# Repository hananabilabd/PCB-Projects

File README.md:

# PCB-Projects
PCB Projects by me using Eagle
## ARM based micro-processor STM32F446RC breakout board 

## STM32F413CG breakout board

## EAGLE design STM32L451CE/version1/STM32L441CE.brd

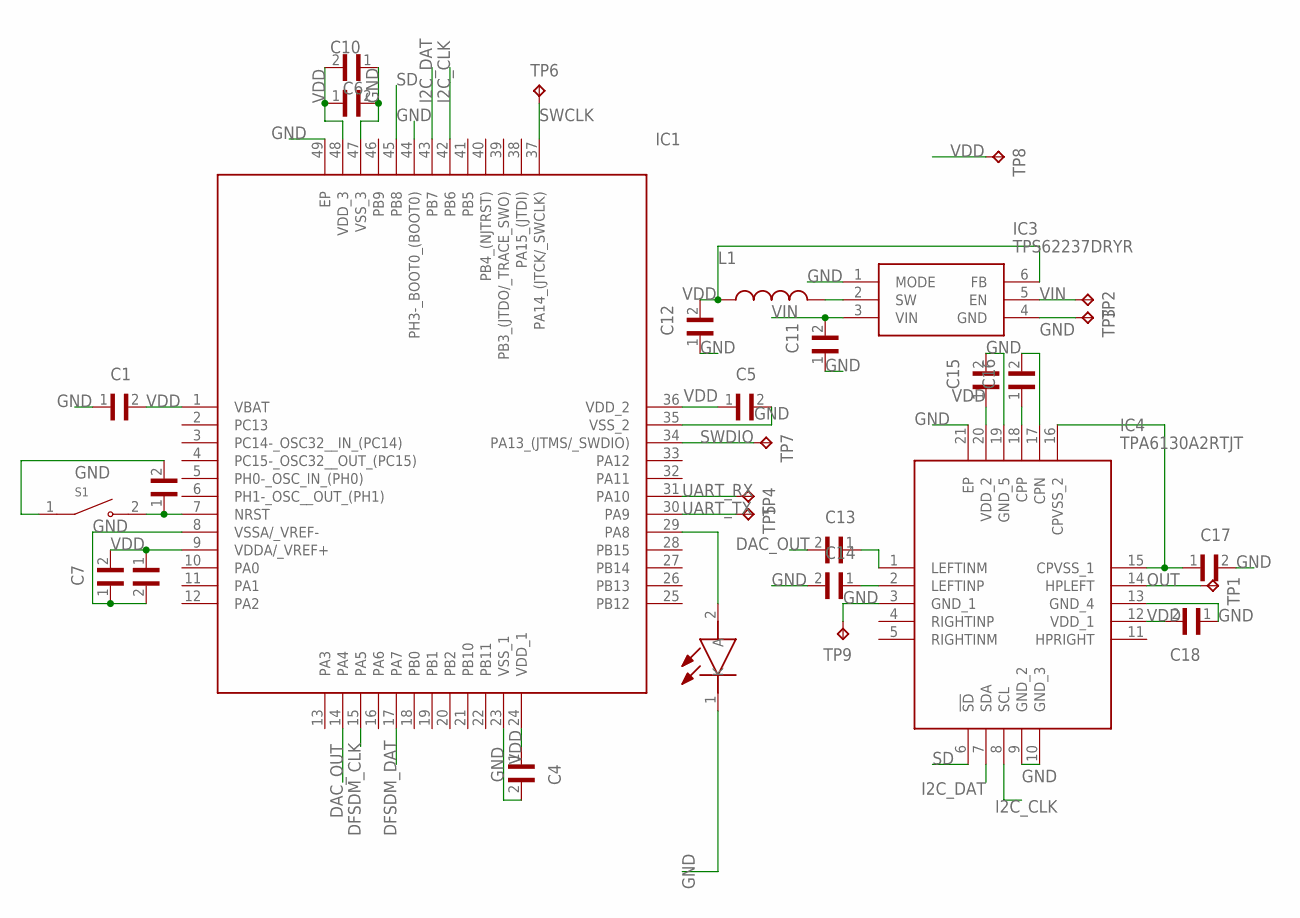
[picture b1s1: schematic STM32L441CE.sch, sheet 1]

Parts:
C1, C2, C3, C4, C5, C6: GRM033C80J104KE15D; CAPC0603X33N
C7, C15, C16, C17, C18: JMK105C6105KV-F; CAPC1005X55N
C10, C12: GRM155R60J475ME47D; CAPC1005X60N
C11: GRM155R60J225KE95D; CAPC1005X55N
C13, C14: CC0402KRX5R5BB474; CAPC1005X55N
IC1: STM32L451CEU6; QFN50P700X700X60-49N
IC3: TPS62237DRYR; SON50P100X145X60-6N
IC4: TPA6130A2RTJT; QFN50P400X400X80-21N
L1: LQM21PN2R2MC0D; INDC2012X55N
LED1: VLMS1500-GS08; VLMG1500GS08
S1: B3U-1000P; SW_B3U-1000P
TP1, TP2, TP3, TP4, TP5, TP6, TP7, TP8, TP9: TPTP11R; TP11R

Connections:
DAC_OUT: C13.2, IC1.14 (PA4)
DFSDM_CLK: IC1.15 (PA5); also elsewhere on the board
DFSDM_DAT: IC1.17 (PA7); also elsewhere on the board
GND: C1.1, C2.2, C3.2, C4.2, C5.2, C6.2, C7.1, C10.1, C11.1, C12.1, C14.2, C15.2, C17.2, C18.1, IC1.8 (VSSA/_VREF-), IC1.23 (VSS_1), IC1.35 (VSS_2), IC1.44 (PH3-_BOOT0_(BOOT0)), IC1.47 (VSS_3), IC1.49 (EP), IC3.1 (MODE), IC3.4 (GND), IC4.3 (GND_1), IC4.9 (GND_2), IC4.10 (GND_3), IC4.13 (GND_4), IC4.19 (GND_5), IC4.21 (EP), LED1.1 (K), S1.1, TP3.TP, TP9.TP; also elsewhere on the board
I2C_CLK: IC1.42 (PB6), IC4.8 (SCL)
I2C_DAT: IC1.43 (PB7), IC4.7 (SDA)
unnamed: C2.1, IC1.7 (NRST), S1.2
unnamed: IC3.2 (SW), L1.2
unnamed: C13.1, IC4.1 (LEFTINM)
unnamed: C14.1, IC4.2 (LEFTINP)
unnamed: IC1.29 (PA8), LED1.2 (A)
unnamed: C16.1, IC4.18 (CPP)
unnamed: C16.2, IC4.17 (CPN)
unnamed: C17.1, IC4.15 (CPVSS_1), IC4.16 (CPVSS_2)
OUT: IC4.14 (HPLEFT), TP1.TP
SD: IC1.45 (PB8), IC4.6 (!SD)
SWCLK: IC1.37 (PA14_(JTCK/_SWCLK)), TP6.TP
SWDIO: IC1.34 (PA13_(JTMS/_SWDIO)), TP7.TP
UART_RX: IC1.31 (PA10), TP4.TP
UART_TX: IC1.30 (PA9), TP5.TP
VDD: C1.2, C3.1, C4.1, C5.1, C6.1, C7.2, C10.2, C12.2, C15.1, C18.2, IC1.1 (VBAT), IC1.9 (VDDA/_VREF+), IC1.24 (VDD_1), IC1.36 (VDD_2), IC1.48 (VDD_3), IC3.6 (FB), IC4.12 (VDD_1), IC4.20 (VDD_2), L1.1, TP8.TP; also elsewhere on the board
VIN: C11.2, IC3.3 (VIN), IC3.5 (EN), TP2.TP

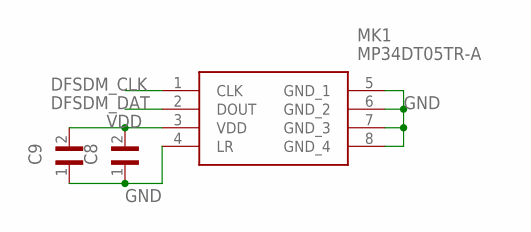
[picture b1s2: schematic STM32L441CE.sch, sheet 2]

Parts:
C8: JMK105C6105KV-F; CAPC1005X55N
C9: GRM033C80J104KE15D; CAPC0603X33N
MK1: MP34DT05TR-A; MP34DT05TRA

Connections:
DFSDM_CLK: MK1.1 (CLK); also elsewhere on the board
DFSDM_DAT: MK1.2 (DOUT); also elsewhere on the board
GND: C8.1, C9.1, MK1.4 (LR), MK1.5 (GND_1), MK1.6 (GND_2), MK1.7 (GND_3), MK1.8 (GND_4); also elsewhere on the board
VDD: C8.2, C9.2, MK1.3 (VDD); also elsewhere on the board

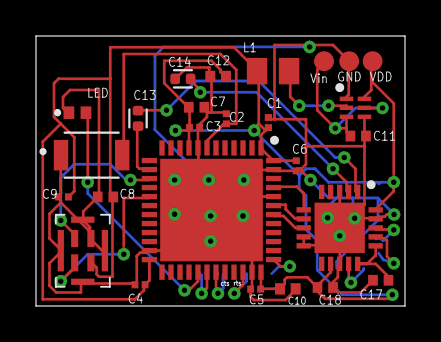
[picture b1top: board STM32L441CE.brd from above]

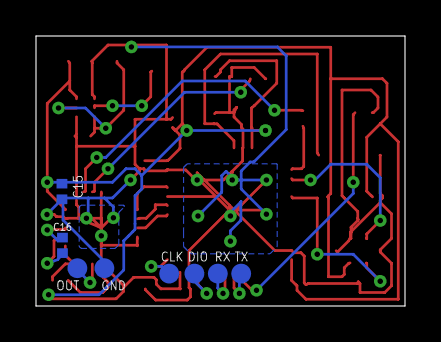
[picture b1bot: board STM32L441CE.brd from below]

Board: 2 copper layers, 20.5 x 15.0 mm, 34 parts (8 on the bottom side), 22 nets.

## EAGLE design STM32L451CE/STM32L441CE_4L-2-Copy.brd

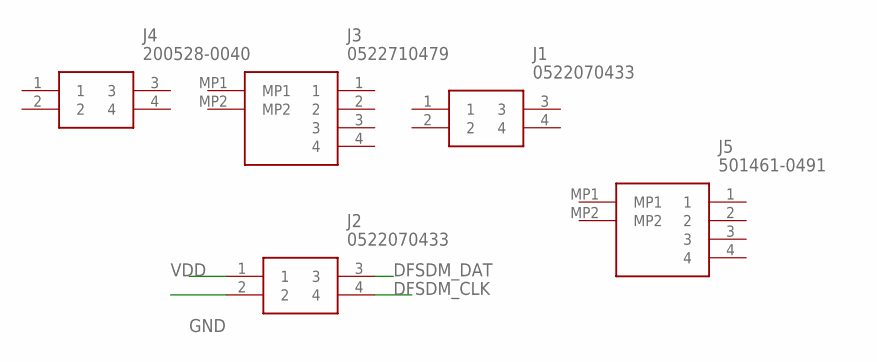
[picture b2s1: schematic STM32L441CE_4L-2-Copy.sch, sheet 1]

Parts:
J1, J2: 0522070433
J3: 0522710479
J4: 200528-0040
J5: 501461-0491; 5014610491

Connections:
DFSDM_CLK: J2.4; also elsewhere on the board
DFSDM_DAT: J2.3; also elsewhere on the board
GND: J2.2; also elsewhere on the board
VDD: J2.1; also elsewhere on the board

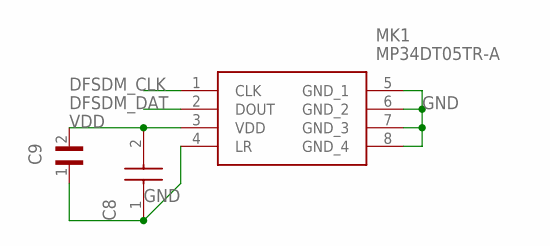
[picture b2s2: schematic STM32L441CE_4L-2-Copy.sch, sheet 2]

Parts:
C8: AMK063AC6105KP-F; CAPC0603X33N
C9: GRM033C80J104KE15D; CAPC0603X33N
MK1: MP34DT05TR-A; MP34DT05TRA

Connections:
DFSDM_CLK: MK1.1 (CLK); also elsewhere on the board
DFSDM_DAT: MK1.2 (DOUT); also elsewhere on the board
GND: C8.1, C9.1, MK1.4 (LR), MK1.5 (GND_1), MK1.6 (GND_2), MK1.7 (GND_3), MK1.8 (GND_4); also elsewhere on the board
VDD: C8.2, C9.2, MK1.3 (VDD); also elsewhere on the board

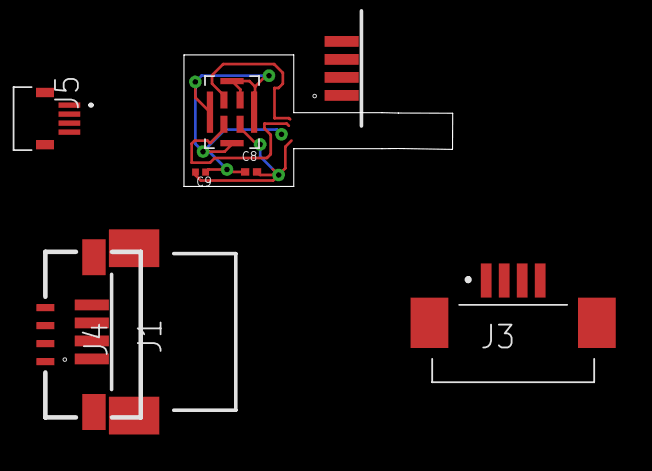
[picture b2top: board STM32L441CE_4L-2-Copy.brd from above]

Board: 4 copper layers, 14.9 x 7.3 mm, 8 parts (0 on the bottom side), 4 nets.

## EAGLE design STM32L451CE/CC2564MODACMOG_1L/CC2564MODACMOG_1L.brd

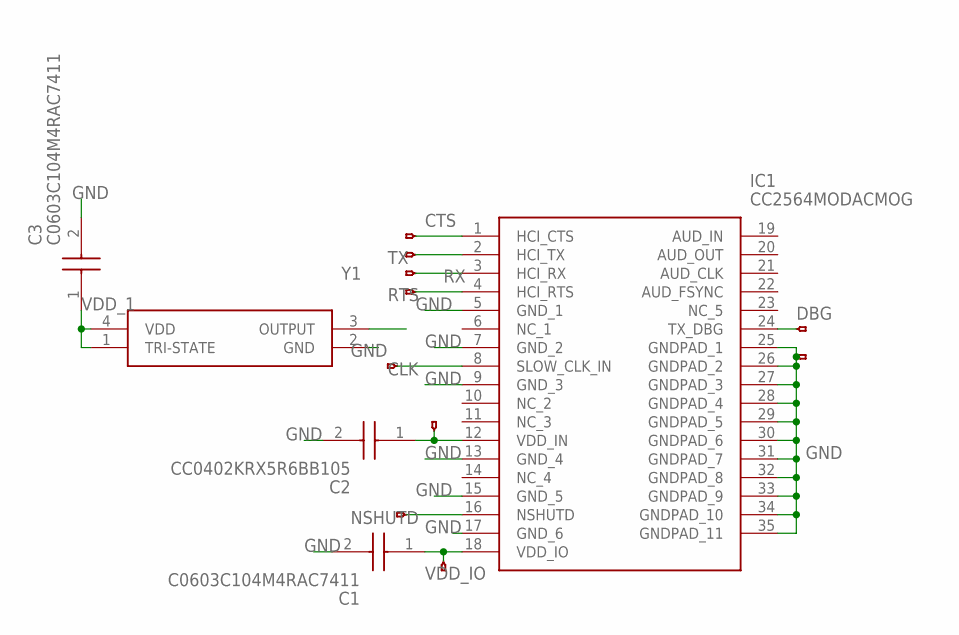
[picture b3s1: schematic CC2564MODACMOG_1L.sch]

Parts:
C1, C3: C0603C104M4RAC7411; CAPC1608X95N
C2: CC0402KRX5R6BB105; CAPC1005X55N
IC1: CC2564MODACMOG; MOG0035A
JP1, JP2, JP7, JP8, JP9, JP10, JP11, JP12, JP13, JP14: HEADERHOLE-HEADERHOLE; 1X1-HEADER-HOLE
Y1: ECS-327MVATX-1-CN-TR; ECS327MVATX1CNTR

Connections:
CLK: IC1.8 (SLOW_CLK_IN), JP11.1
CTS: IC1.1 (HCI_CTS), JP7.1
DBG: IC1.24 (TX_DBG), JP2.1
GND: C1.2, C2.2 (C2), C3.2, IC1.5 (GND_1), IC1.7 (GND_2), IC1.9 (GND_3), IC1.13 (GND_4), IC1.15 (GND_5), IC1.17 (GND_6), IC1.25 (GNDPAD_1), IC1.26 (GNDPAD_2), IC1.27 (GNDPAD_3), IC1.28 (GNDPAD_4), IC1.29 (GNDPAD_5), IC1.30 (GNDPAD_6), IC1.31 (GNDPAD_7), IC1.32 (GNDPAD_8), IC1.33 (GNDPAD_9), IC1.34 (GNDPAD_10), IC1.35 (GNDPAD_11), JP1.1, Y1.2 (GND)
NSHUTD: IC1.16 (NSHUTD), JP14.1
RTS: IC1.4 (HCI_RTS), JP10.1
RX: IC1.3 (HCI_RX), JP9.1
TX: IC1.2 (HCI_TX), JP8.1
VDD: C2.1 (C1), IC1.12 (VDD_IN), JP12.1
VDD_1: C3.1, Y1.1 (TRI-STATE), Y1.4 (VDD)
VDD_IO: C1.1, IC1.18 (VDD_IO), JP13.1

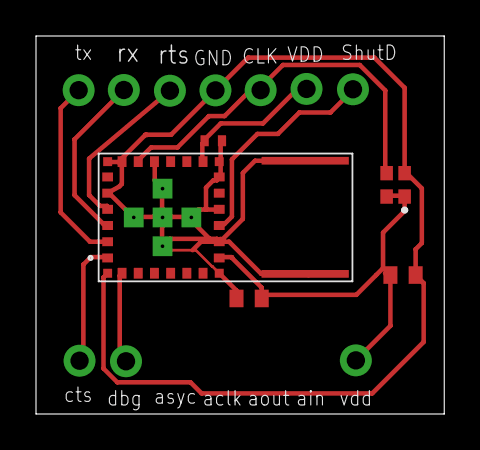
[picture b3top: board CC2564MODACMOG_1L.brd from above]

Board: 2 copper layers, 22.7 x 21.0 mm, 15 parts (0 on the bottom side), 11 nets.

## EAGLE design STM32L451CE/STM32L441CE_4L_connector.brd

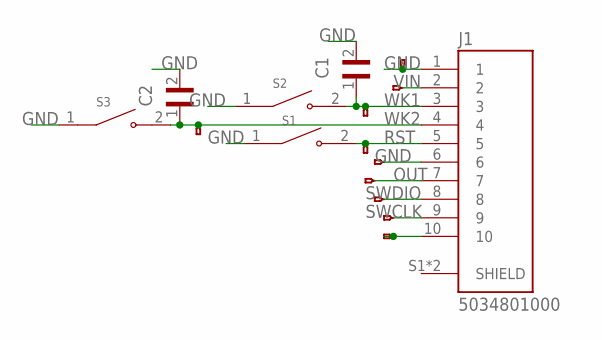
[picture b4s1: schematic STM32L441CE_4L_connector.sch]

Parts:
C1, C2: GRM033C80J104KE15D; CAPC0603X33N
J1: 5034801000; MOLEX_5034801000
JP1, JP2, JP3, JP4, JP5, JP6, JP7, JP8, JP9, JP10: HEADERHOLE-HEADERHOLE; 1X1-HEADER-HOLE
S1, S2, S3: B3U-1000P; SW_B3U-1000P

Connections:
GND: C1.2, C2.2, J1.1, J1.6, JP1.1, JP10.1, S1.1, S2.1, S3.1
unnamed: J1.10, JP5.1
OUT: J1.7, JP2.1
RST: J1.5, JP6.1, S1.2
SWCLK: J1.9, JP4.1
SWDIO: J1.8, JP3.1
VIN: J1.2, JP9.1
WK1: C1.1, J1.3, JP8.1, S2.2
WK2: C2.1, J1.4, JP7.1, S3.2

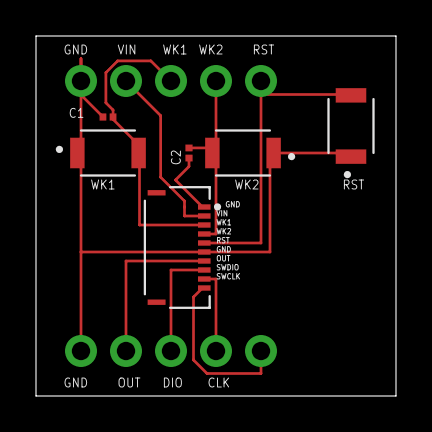
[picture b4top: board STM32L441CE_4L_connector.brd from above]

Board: 2 copper layers, 20.0 x 20.0 mm, 16 parts (0 on the bottom side), 9 nets.

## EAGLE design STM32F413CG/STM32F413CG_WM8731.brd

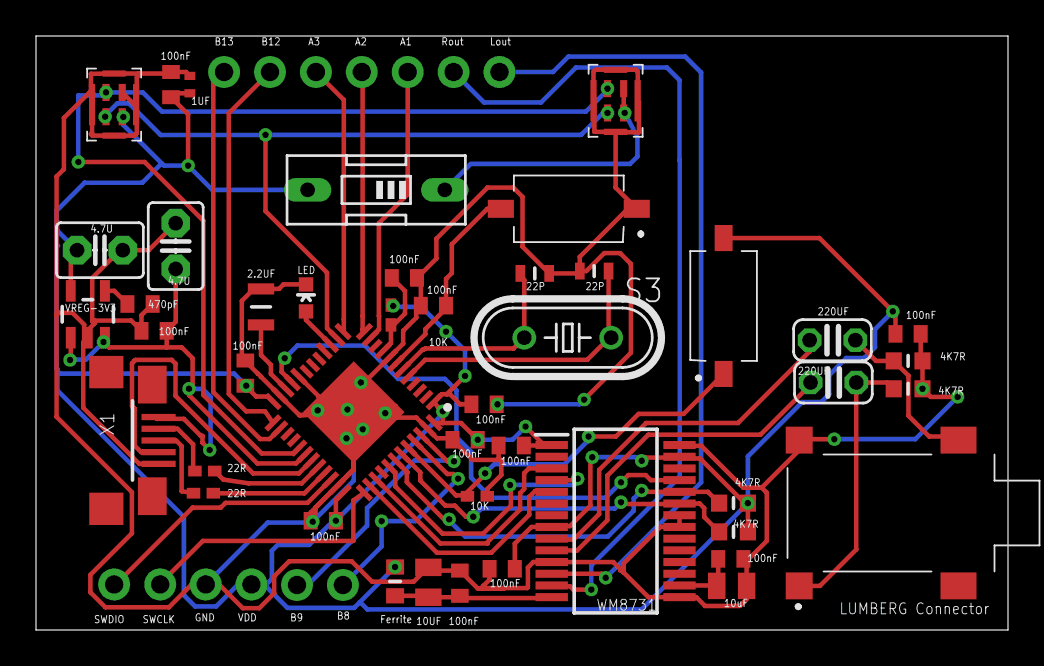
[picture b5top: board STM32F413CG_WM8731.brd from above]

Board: 2 copper layers, 54.0 x 33.0 mm, 58 parts (0 on the bottom side), 42 nets.

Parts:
C1, C15, C19, C22: C0603C104M4RAC7411; CAPC1608X95N
C2, C4: 22P; CAPC1608X80N
C3, C5, C6, C7, C8, C12, C13, C14: 100n; CAPC1608X95N
C9, C11: 4.7u; C2.5-3
C10: 470p; CAPC1608X87N
C16, C17: 220UF; C025-024X044
C18: 1UF; CAPC1005X55N
C20: CL21A106KAYNNNE_10UF; CAPC2012X145N
C21: CL21A106KAYNNNE; CAPC2012X145N
C33: 100nf; CAPC1608X95N
C38: 2.2UF; CAPC2012X145N
FB1: BLM18BD252SN1D; BEADC1608X95N
IC1: STM32F413CGU6; QFN50P700X700X60-49N
IC2: WM8731SEDS_RV; SOP65P780X200-28N
J2: 1503_02; 150302
JP1, JP2, JP3, JP4, JP5, JP6, JP7, JP8, JP9, JP10, JP11, JP12, JP13: 1X1-HEADER-HOLE
LED2: LED-0603
MK1, MK2: MP34DT05TR-A; MP34DT05TRA
Q1: HC49/S
R2: 10K; RESC1005X40N
R3: CRCW040222R0FKED; RESC1005X40N
R4, R7, R8, R9: CR0603-JW-472ELF; RESC1608X55N
R5, R6: 22R; RESC1005X40N
S1, S3: PTS636_SK25J_SMTR_LFS; PTS636SK25JSMTRLFS
SW1: EDG-01
VREG-3V3: V_REG_LDOSMD; SOT23-5
X1: USB-MICROB-SMD

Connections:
5V: C9.2, C12.2, IC1.30, VREG-3V3.1, VREG-3V3.3, X1.VBUS
A1: IC1.11, JP8.1
A2: IC1.12, JP9.1
A3: IC1.13, JP10.1
A4: IC1.14, MK1.2, MK2.2
A5: IC1.15, LED2.A
A8: IC1.29, MK1.1, MK2.1
A15: IC1.38, IC2.5
B3: IC1.39, IC2.3
B5: IC1.41, IC2.4
B6: IC1.42, IC2.24, R4.2
B7: IC1.43, IC2.23, R7.2
B8: IC1.45, JP5.1
B9: IC1.46, JP11.1
B10: IC1.21, IC2.25
B12: IC1.25, JP7.1
B13: IC1.26, JP6.1
GND: C1.2, C2.1, C3.1, C4.1, C5.1, C6.2, C7.1, C8.2, C9.1, C10.1, C11.1, C12.1, C13.2, C14.1, C15.1, C18.2, C19.1, C20.1, C21.2, C22.1, C33.2, C38.2, IC1.8, IC1.20, IC1.23, IC1.35, IC1.47, IC1.49, IC2.11, IC2.15, IC2.21, IC2.22, IC2.28, J2.4, JP1.1, LED2.C, MK1.4, MK1.5, MK1.6, MK1.7, MK1.8, MK2.5, MK2.6, MK2.7, MK2.8, R2.2, R8.2, R9.2, S3.1, VREG-3V3.2, X1.GND
LHP: C16.1, IC2.9
unnamed: C2.2, IC1.5, Q1.2
unnamed: MK2.3, MK2.4, SW1.1
unnamed: C3.2, IC1.7, S3.2
unnamed: C10.2, VREG-3V3.4
unnamed: C7.2, IC1.9, R3.2
unnamed: C16.2, J2.3, R8.1
unnamed: R5.2, X1.D-
unnamed: IC1.31, X1.ID
unnamed: IC1.32, R5.1
unnamed: R6.2, X1.D+
unnamed: IC1.33, R6.1
unnamed: C19.2, C20.2, FB1.2, IC2.14
unnamed: IC1.44, R2.1, S1.1
unnamed: C21.1, C22.2, IC2.16
unnamed: IC2.12, JP13.1
unnamed: IC2.13, JP12.1
unnamed: C4.2, IC1.6, Q1.1
unnamed: C17.2, J2.1, R9.1
unnamed: C38.1, IC1.22
RHP: C17.1, IC2.10
SWCLK: IC1.37, JP2.1
SWDIO: IC1.34, JP3.1
VDD: C1.1, C5.2, C6.1, C8.1, C11.2, C13.1, C14.2, C15.2, C18.1, C33.1, FB1.1, IC1.1, IC1.24, IC1.36, IC1.48, IC2.1, IC2.8, IC2.27, JP4.1, MK1.3, R3.1, R4.1, R7.1, S1.2, SW1.2, VREG-3V3.5

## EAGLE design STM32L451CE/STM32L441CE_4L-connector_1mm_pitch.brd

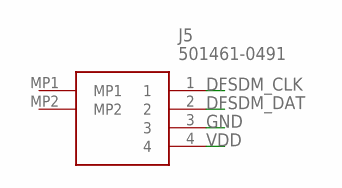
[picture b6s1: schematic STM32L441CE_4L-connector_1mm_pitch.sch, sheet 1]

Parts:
J5: 501461-0491; 5014610491

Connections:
DFSDM_CLK: J5.1; also elsewhere on the board
DFSDM_DAT: J5.2; also elsewhere on the board
GND: J5.3; also elsewhere on the board
VDD: J5.4; also elsewhere on the board

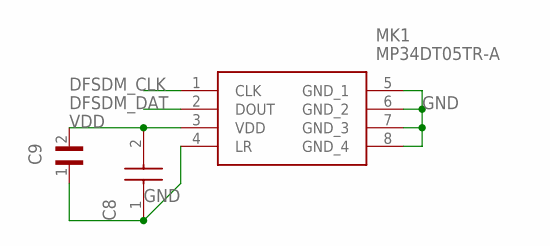
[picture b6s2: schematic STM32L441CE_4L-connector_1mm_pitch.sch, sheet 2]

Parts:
C8: AMK063AC6105KP-F; CAPC0603X33N
C9: GRM033C80J104KE15D; CAPC0603X33N
MK1: MP34DT05TR-A; MP34DT05TRA

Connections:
DFSDM_CLK: MK1.1 (CLK); also elsewhere on the board
DFSDM_DAT: MK1.2 (DOUT); also elsewhere on the board
GND: C8.1, C9.1, MK1.4 (LR), MK1.5 (GND_1), MK1.6 (GND_2), MK1.7 (GND_3), MK1.8 (GND_4); also elsewhere on the board
VDD: C8.2, C9.2, MK1.3 (VDD); also elsewhere on the board

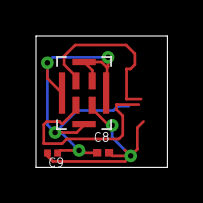
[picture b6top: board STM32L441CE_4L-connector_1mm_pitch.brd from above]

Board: 4 copper layers, 7.3 x 7.3 mm, 4 parts (1 on the bottom side), 4 nets.

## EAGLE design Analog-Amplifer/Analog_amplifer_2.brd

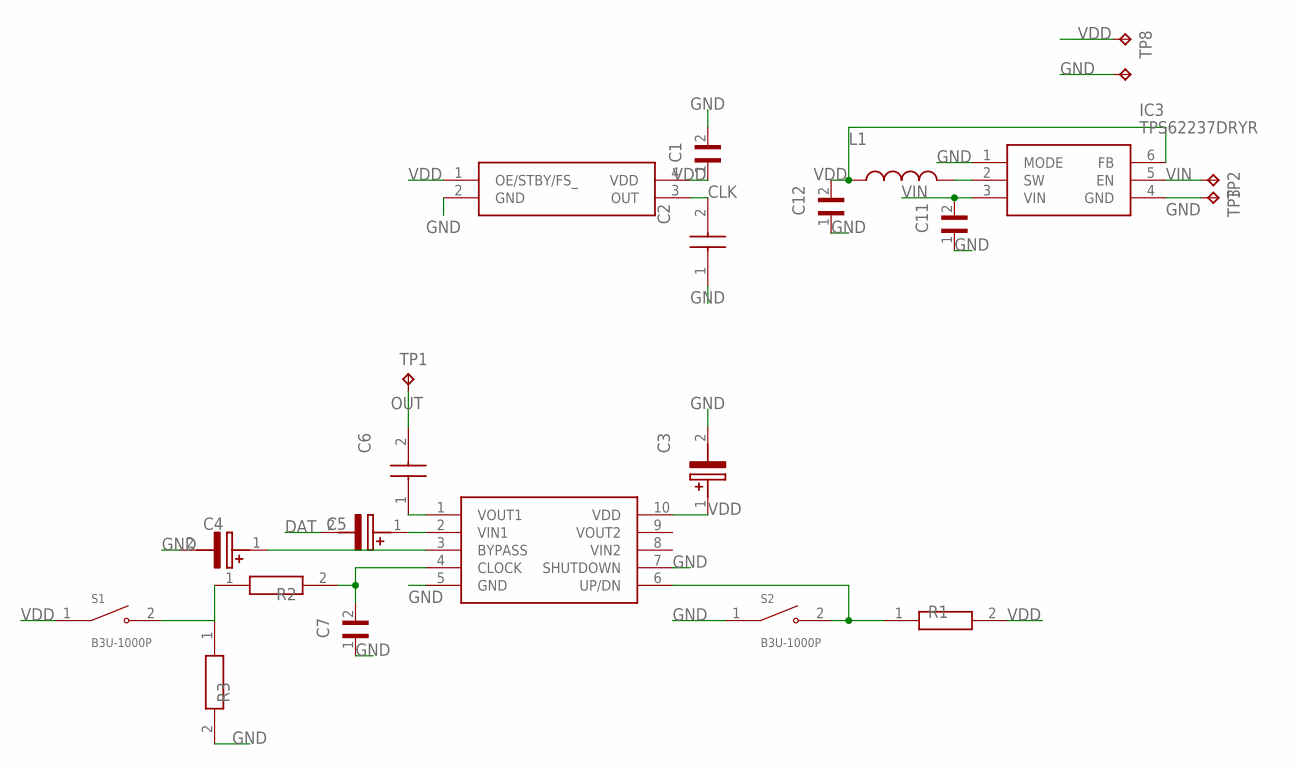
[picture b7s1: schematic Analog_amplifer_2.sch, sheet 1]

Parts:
C1, C7: GRM033C80J104KE15D; CAPC0603X33N
C2: GRM0115C1E5R0CE01L; CAPC0201X14N
C3, C4, C5: F380J105MUA; CAPPC1106X60N
C6: GRM21BR60J107ME15L; CAPC2012X145N
C11: GRM155R60J225KE95D; CAPC1005X55N
C12: GRM155R60J475ME47D; CAPC1005X60N
IC1: LM4811MM_NOPB; SOP50P490X110-10N
IC3: TPS62237DRYR; SON50P100X145X60-6N
L1: LQM21PN2R2MC0D; INDC2012X55N
R1: RC0201FR-074K02L; RESC0603X26N
R2, R3: RC0201FR-07100RL; RESC0603X26N
S1, S2: B3U-1000P; SW_B3U-1000P
TP1, TP2, TP3, TP4, TP8: TPTP11R; TP11R
Y1: DSC6053CE2A-003.0720; DSC6053CE2A0030720

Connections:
CLK: C2.2, Y1.3 (OUT); also elsewhere on the board
DAT: C5.2 (-); also elsewhere on the board
GND: C1.2, C2.1, C3.2 (-), C4.2 (-), C7.1, C11.1, C12.1, IC1.5 (GND), IC1.7 (SHUTDOWN), IC3.1 (MODE), IC3.4 (GND), R3.2, S2.1, TP3.TP, TP4.TP, Y1.2 (GND); also elsewhere on the board
unnamed: C4.1 (+), IC1.3 (BYPASS)
unnamed: IC3.2 (SW), L1.2
unnamed: C6.1, IC1.1 (VOUT1)
unnamed: C7.2, IC1.4 (CLOCK), R2.2
unnamed: C5.1 (+), IC1.2 (VIN1)
unnamed: IC1.6 (UP/DN), R1.1, S2.2
unnamed: R2.1, R3.1, S1.2
OUT: C6.2, TP1.TP
VDD: C1.1, C3.1 (+), C12.2, IC1.10 (VDD), IC3.6 (FB), L1.1, R1.2, S1.1, TP8.TP, Y1.1 (OE/STBY/FS_), Y1.4 (VDD); also elsewhere on the board
VIN: C11.2, IC3.3 (VIN), IC3.5 (EN), TP2.TP

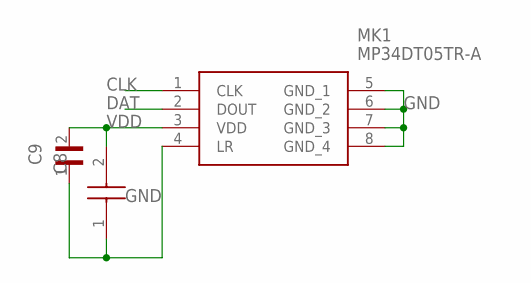
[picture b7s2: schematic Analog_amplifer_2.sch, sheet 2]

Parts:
C8: C0402C105K9PACTU; CAPC1005X55N
C9: GRM033C80J104KE15D; CAPC0603X33N
MK1: MP34DT05TR-A; MP34DT05TRA

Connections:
CLK: MK1.1 (CLK); also elsewhere on the board
DAT: MK1.2 (DOUT); also elsewhere on the board
GND: C8.1, C9.1, MK1.4 (LR), MK1.5 (GND_1), MK1.6 (GND_2), MK1.7 (GND_3), MK1.8 (GND_4); also elsewhere on the board
VDD: C8.2, C9.2, MK1.3 (VDD); also elsewhere on the board

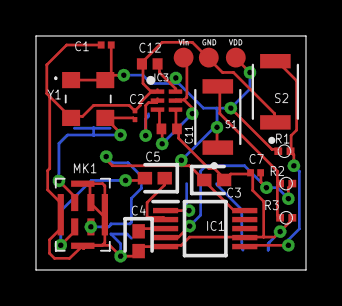
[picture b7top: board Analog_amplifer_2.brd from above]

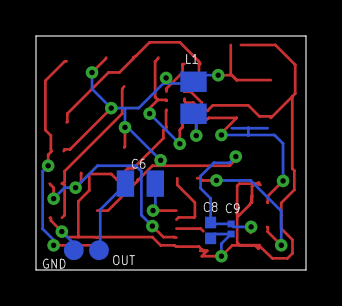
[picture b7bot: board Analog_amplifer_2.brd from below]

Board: 2 copper layers, 15.0 x 13.0 mm, 26 parts (6 on the bottom side), 13 nets.

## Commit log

2019-03-28 added
2019-04-22 version2
2019-06-15 added double layer
2019-06-22 added new PCB design of STM32F413CG
2019-06-22 final stage
2019-07-05 added final
2019-07-05 added greb
2020-01-17 added photos
2020-02-02 adjusted some smd components
2020-02-22 latest
2020-02-22 solve
2020-07-16 added STM32L451RE
2020-07-16 added .zip
2020-07-16 deleted some unneeded files
2020-07-31 added analog amplifier
2020-07-31 update gerber
2020-08-03 added right view
2020-09-25 added schematic image
